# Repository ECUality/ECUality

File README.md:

# ECUality

This project is about taking full control of a dated fuel-injection system, and making that process easier to repeat. Currently, the system is built to run the engine in a 1984 VW vanagon. I aim to create a platform that bears adaptation requiring a minimum of external tools. 

ECUality differs from other ECU projects in that I avoid relying on complex tuning software, favoring simple map-tuning algorithms that run whenever the engine and O2 sensor are warm. 

More info [here](https://hackaday.io/project/4622-ecuality1).

## Install

1. Install the [Arduino IDE](https://www.arduino.cc/en/Main/Donate).
2. Clone the repository.
3. Connect an Arduino Mega 2560 to your computer's USB port.
4. Start the Arduino IDE.
5. Open `ECUality.ino` in the IDE.
6. Click "Upload". This will build the project, and upload the compiled firmware to your Arduino.

## License
[GNU GPLv3](LICENSE.txt)

## Dependencies
Platform: 8-bit Arduino Mega 2560 (The chip is AtMega 2560), atop the ECU shield specified in the shcematic and layout files.  
Build: Arduino IDE (uses gcc toolchain)

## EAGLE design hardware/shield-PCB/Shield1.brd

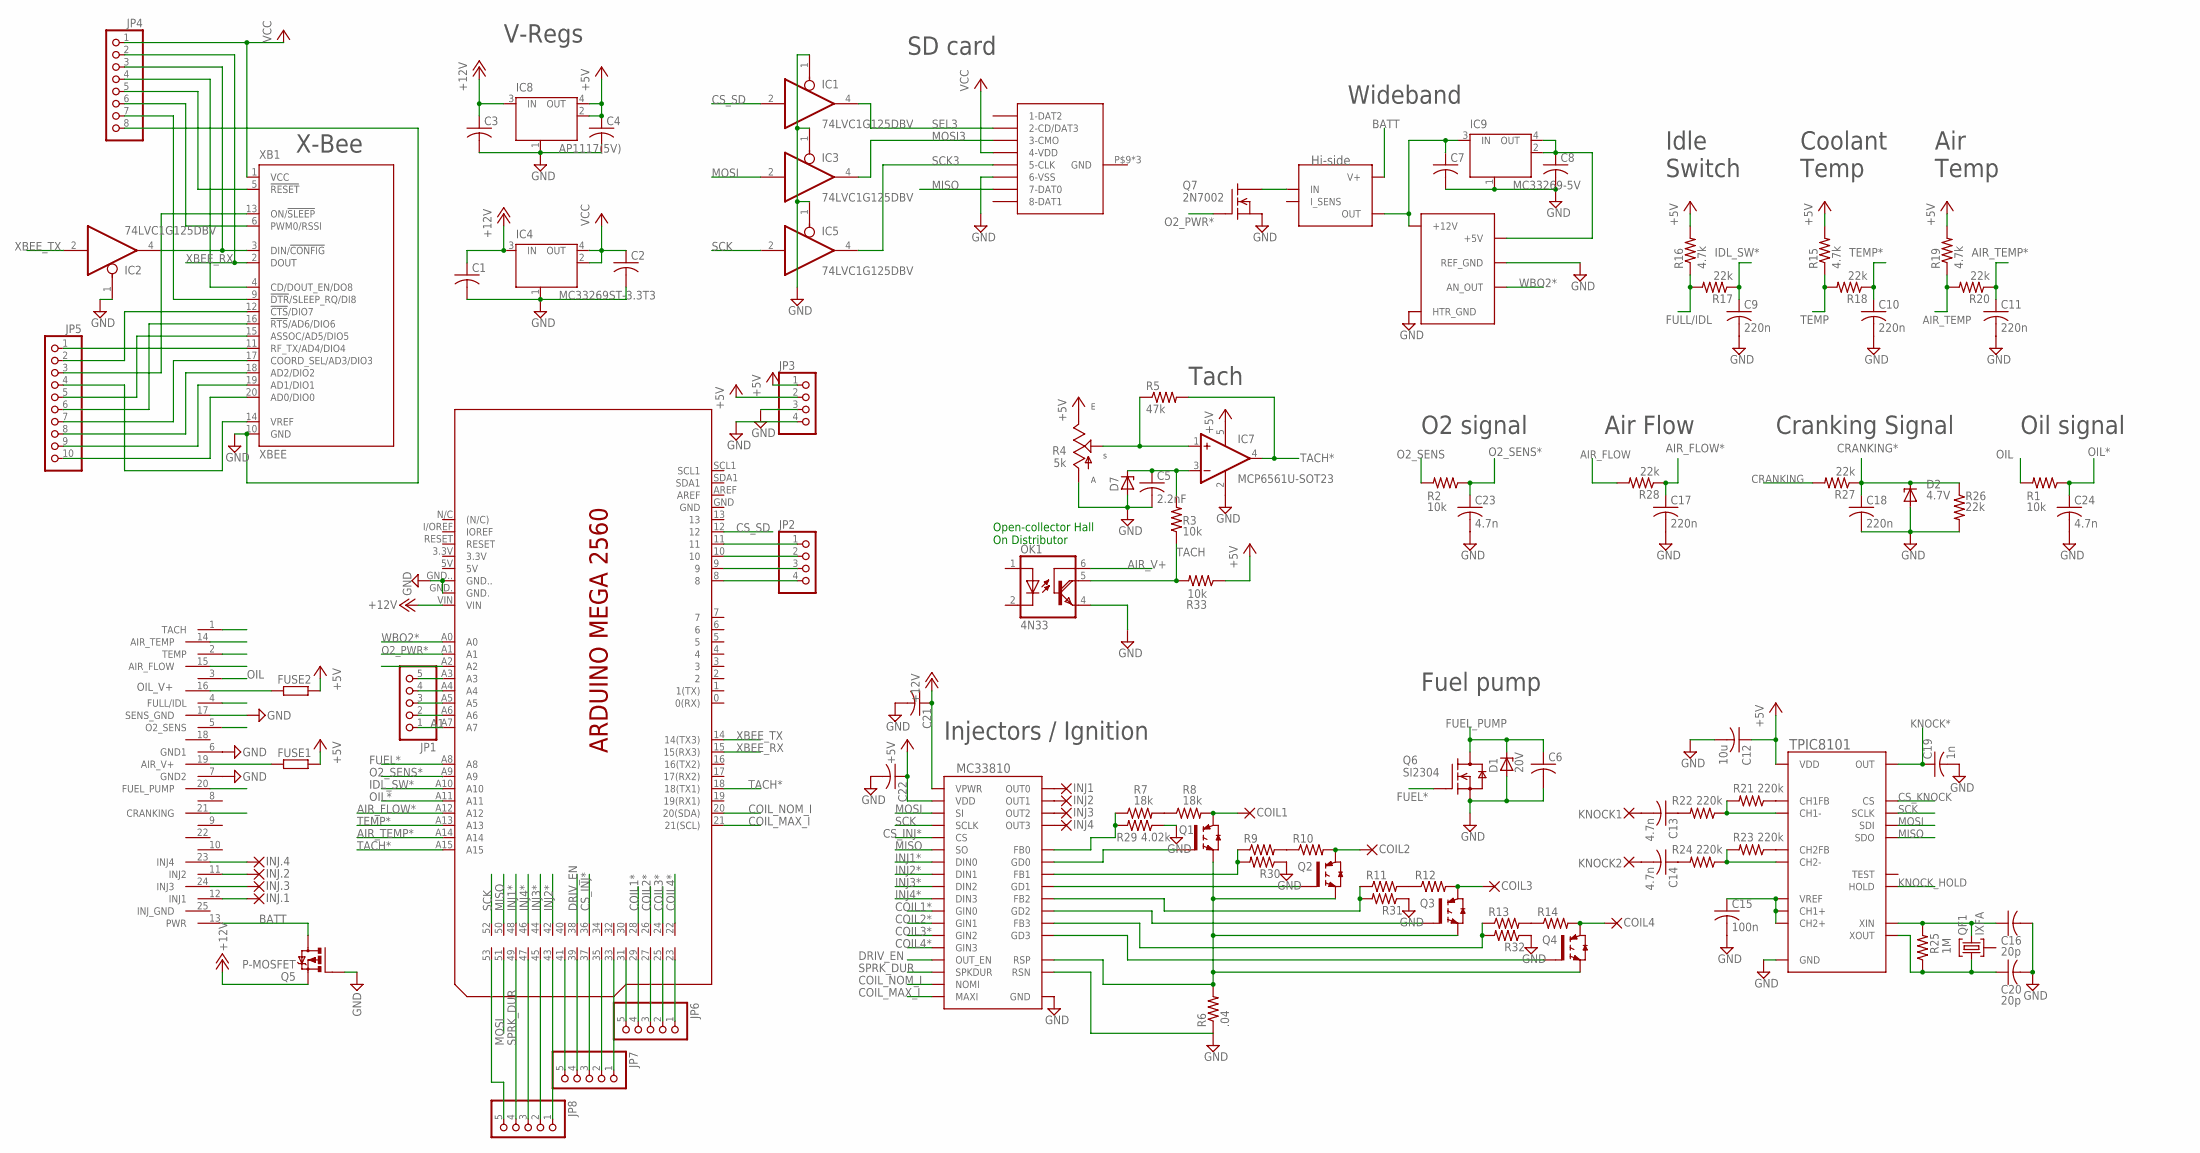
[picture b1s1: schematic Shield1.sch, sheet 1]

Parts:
C1, C2, C3, C4, C6, C7, C8, C21, C22: C-USC1206; C1206
C5: 2.2nF; C1206
C9, C10, C11, C17, C18: 220n; C1206
C12: 10u; C1206
C13, C14, C23, C24: 4.7n; C1206
C15: 100n; C1206
C16, C20: 20p; C1206
C19: 1n; C1206
COIL1, COIL2, COIL3, COIL4: 2,15/1,0
D1: 20V; SOD123
D2: 4.7V; SOD123
D7: ZENER-DIODESOD80C; SOD80C
FUSE1, FUSE2: R-EU_R1206W; R1206W
IC1, IC2, IC3, IC5: 74LVC1G125DBV; SOT23-5
IC4: MC33269ST-3.3T3; SOT223
IC6: MC33810SSOP; SSOP32_POWERPAD
IC7: MCP6561U-SOT23; SOT23-5
IC8: AP1117(5V); SOT223
IC9: MC33269-5V; SOT223
IC11: KNOCK_SENS_IC_TPIC8101; SO20L
INJ1, INJ2, INJ3, INJ4, INJ.1, INJ.2, INJ.3, INJ.4: 2,15/1,2
JP1, JP6, JP7, JP8: PINHD-1X5; 1X05
JP2, JP3: PINHD-1X4; 1X04
JP4: PINHD-1X8; 1X08
JP5: PINHD-1X10NARROW; 1X10-N
KNOCK1, KNOCK2: 2,15/1,0
OK1: 4N33; DIL06
Q1, Q2, Q3, Q4: ISL9V5036S3S; D2PACK
Q5: P-MOSFET; D-PAK_TO252AA
Q6: SI2304; SOT23
Q7: 2N7002; SOT23
Q8: BTS6133; DPACK_5
QF1: IXFA; HC49U
R1, R2, R3, R33: 10k; R1206
R4: 5k; 50/45J
R5: 47k; R1206
R6: .04; 0840/27
R7, R8: 18k; R1210W
R9, R10, R11, R12, R13, R14: R-US_R1210W; R1210W
R15, R16, R19: 4.7k; R1206
R17, R18, R20, R26, R27, R28: 22k; R1206
R21, R22, R23, R24: 220k; R1206
R25: 1M; R1206
R29: 4.02k; R1206
R30, R31, R32: R-US_R1206; R1206
U$1: VW_84_CONN
U$3: HI-ROSE-DM3D; DM3D-SF
U$4: ECOTRON_ALM-BOARD; ECOTRONS_ALM-BOARD
U$9: MEGA2560_SMD; MEGA_NO-PWR/USB/ICSP_SMD
XB1: XBEE

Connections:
+5V: C4.1, C12.1, C22.1, FUSE1.2, FUSE2.2, IC6.8 (VDD), IC7.5 (V+), IC8.2 (OUT), IC8.4 (OUT), IC11.1 (VDD), JP3.1, JP3.2, R4.1 (E), R15.2, R16.2, R19.2, R33.1
+12V: C1.1, C3.1, C21.1, IC4.3 (IN), IC6.25 (VPWR), IC8.3 (IN), Q5.3 (S), U$9.VIN
A1: JP1.1, U$9.A7
AIR_FLOW: R28.2, U$1.15 (AIR_FLOW)
AIR_FLOW*: C17.1, R28.1, U$9.A12
AIR_TEMP: R19.1, R20.2, U$1.14 (AIR_TEMP)
AIR_TEMP*: C11.1, R20.1, U$9.A14
AIR_V+: FUSE1.1, OK1.6 (B), U$1.19 (AIR_V+)
BATT: Q5.4 (D), Q8.3 (V+), U$1.13 (PWR)
COIL1: COIL1.1, Q1.2 (C), R8.2
COIL1*: IC6.24 (GIN0), U$9.28
COIL2: COIL2.1, Q2.2 (C), R10.2
COIL2*: IC6.23 (GIN1), U$9.26
COIL3: COIL3.1, Q3.2 (C), R12.2
COIL3*: IC6.22 (GIN2), U$9.24
COIL4: COIL4.1, Q4.2 (C), R14.2
COIL4*: IC6.21 (GIN3), U$9.22
COIL_MAX_I: IC6.29 (MAXI), U$9.21 (21(SCL))
COIL_NOM_I: IC6.28 (NOMI), U$9.20 (20(SDA))
CRANKING: R27.2, U$1.21 (CRANKING)
CRANKING*: C18.1, D2.C, R26.1, R27.1
CS_INJ*: IC6.4 (CS), U$9.36
CS_KNOCK: IC11.8 (CS)
CS_SD: IC1.2 (I), U$9.12
DRIV_EN: IC6.9 (OUT_EN), U$9.38
FUEL*: Q6.1 (G), U$9.A8
FUEL_PUMP: C6.1, D1.C, Q6.3 (D), U$1.20 (FUEL_PUMP)
FULL/IDL: R16.1, R17.2, U$1.4 (FULL/IDL)
GND: C1.2, C2.2, C3.2, C4.2, C5.2, C6.2, C7.2, C8.2, C9.2, C10.2, C11.2, C12.2, C15.2, C16.2, C17.2, C18.2, C19.2, C20.2, C21.2, C22.2, C23.2, C24.2, D1.A, D2.A, D7.A, IC1.1 (OE), IC1.3 (GND), IC2.1 (OE), IC2.3 (GND), IC3.1 (OE), IC3.3 (GND), IC4.1 (GND/ADJ), IC5.1 (OE), IC5.3 (GND), IC6.27 (RSN), IC6.GND, IC6.V1 (GND), IC6.V2 (GND), IC6.V3 (GND), IC6.V4 (GND), IC6.V5 (GND), IC7.2 (V-), IC8.1 (GND/ADJ), IC9.1 (GND/ADJ), IC11.2 (GND), JP3.3, JP3.4, JP4.8, OK1.4 (E), Q5.1 (G), Q6.2 (S), Q7.2 (S), R4.3 (A), R6.1, R26.2, R29.1, R30.1, R31.1, R32.1, U$1.6 (GND1), U$1.7 (GND2), U$1.17 (SENS_GND), U$3.P$3 (6-VSS), U$3.P$9 (GND), U$3.P$10 (GND), U$3.P$11 (GND), U$4.P$2 (HTR_GND), U$4.P$3 (REF_GND), U$4.P$6 (REF_GND), U$4.P$9 (HTR_GND), U$9.GND., U$9.GND.., XB1.10 (GND)
IDL_SW*: C9.1, R17.1, U$9.A10
INJ1: INJ.1.1, U$1.12 (INJ1)
INJ1*: IC6.10 (DIN0), U$9.48
INJ2: INJ.2.1, U$1.11 (INJ2)
INJ2*: IC6.11 (DIN1), U$9.42
INJ3: INJ.3.1, U$1.24 (INJ3)
INJ3*: IC6.12 (DIN2), U$9.44
INJ4: INJ.4.1, U$1.23 (INJ4)
INJ4*: IC6.13 (DIN3), U$9.46
KNOCK*: C19.1, IC11.4 (OUT), U$9.A2
KNOCK_HOLD: IC11.7 (HOLD)
MISO: IC6.7 (SO), IC11.11 (SDO), U$3.P$2 (7-DAT0), U$9.50
MOSI: IC3.2 (I), IC6.6 (SI), IC11.12 (SDI), U$9.51
MOSI3: IC3.4 (O), U$3.P$6 (3-CMO)
unnamed: C5.1, D7.C, IC7.3 (-IN), R3.2
unnamed: C7.1, IC9.3 (IN), Q8.1 (OUT), Q8.5 (OUT), U$4.P$1 (+12V), U$4.P$10 (+12V)
unnamed: IC6.26 (RSP), Q1.3 (E), Q2.3 (E), Q3.3 (E), Q4.3 (E), R6.2
unnamed: IC6.14 (GD1), Q2.1 (G)
unnamed: IC6.2 (FB0), R7.1, R29.2
unnamed: IC6.3 (GD0), Q1.1 (G)
unnamed: Q7.3 (D), Q8.2 (IN)
unnamed: IC6.1 (OUT0), INJ1.1
unnamed: IC11.19 (CH1-), R21.2, R22.1
unnamed: IC7.1 (+IN), R4.2 (S), R5.1
unnamed: IC6.15 (FB1), R9.1, R30.2
unnamed: IC6.30 (GD2), Q3.1 (G)
unnamed: IC2.4 (O), JP4.3, XB1.3 (DIN/!CONFIG)
unnamed: C8.1, IC9.2 (OUT), IC9.4 (OUT), U$4.P$4 (+5V)
unnamed: IC6.31 (FB2), R11.1, R31.2
unnamed: IC6.19 (GD3), Q4.1 (G)
unnamed: IC11.18 (CH1FB), R21.1
unnamed: IC6.18 (FB3), R13.1, R32.2
unnamed: C13.1, R22.2
unnamed: IC11.16 (CH2-), R23.2, R24.1
unnamed: C14.1, R24.2
unnamed: C15.1, IC11.3 (VREF), IC11.15 (CH2+), IC11.20 (CH1+)
unnamed: IC11.17 (CH2FB), R23.1
unnamed: IC6.16 (OUT1), INJ2.1
unnamed: IC6.32 (OUT2), INJ3.1
unnamed: C20.1, IC11.10 (XOUT), QF1.1, R25.1
unnamed: C16.1, IC11.9 (XIN), QF1.3, R25.2
unnamed: IC6.17 (OUT3), INJ4.1
unnamed: C13.2, KNOCK1.1
unnamed: C14.2, KNOCK2.1
unnamed: JP6.1, U$9.23
unnamed: R7.2, R8.1
unnamed: R9.2, R10.1
unnamed: R11.2, R12.1
unnamed: R13.2, R14.1
unnamed: JP1.2, U$9.A6
unnamed: JP1.3, U$9.A5
unnamed: JP1.4, U$9.A4
unnamed: JP1.5, U$9.A3
unnamed: JP2.1, U$9.11
unnamed: JP2.2, U$9.10
unnamed: JP2.3, U$9.9
unnamed: JP2.4, U$9.8
unnamed: JP4.4, XB1.4 (CD/DOUT_EN/DO8)
unnamed: JP4.5, XB1.5 (!RESET)
unnamed: JP4.6, XB1.6 (PWM0/RSSI)
unnamed: JP5.10, XB1.20 (AD0/DIO0)
unnamed: JP5.9, XB1.19 (AD1/DIO1)
unnamed: JP5.8, XB1.18 (AD2/DIO2)
unnamed: JP5.7, XB1.17 (COORD_SEL/AD3/DIO3)
unnamed: JP5.6, XB1.16 (!RTS!/AD6/DIO6)
unnamed: JP5.5, XB1.15 (ASSOC/AD5/DIO5)
unnamed: JP5.4, XB1.14 (VREF)
unnamed: JP5.3, XB1.13 (ON/!SLEEP)
unnamed: JP5.2, XB1.12 (!CTS!/DIO7)
unnamed: JP5.1, XB1.11 (RF_TX/AD4/DIO4)
unnamed: JP4.7, XB1.9 (!DTR!/SLEEP_RQ/DI8)
unnamed: JP6.2, U$9.25
unnamed: JP6.3, U$9.27
unnamed: JP6.4, U$9.29
unnamed: JP6.5, U$9.31
unnamed: JP7.1, U$9.33
unnamed: JP7.2, U$9.35
unnamed: JP7.3, U$9.37
unnamed: JP7.4, U$9.39
unnamed: JP7.5, U$9.41
unnamed: JP8.1, U$9.43
unnamed: JP8.2, U$9.45
unnamed: JP8.3, U$9.47
unnamed: JP8.5, U$9.53
O2_PWR*: Q7.1 (G), U$9.A1
O2_SENS: R2.2, U$1.5 (O2_SENS)
O2_SENS*: C23.1, R2.1, U$9.A9
OIL: R1.2, U$1.3
OIL*: C24.1, R1.1, U$9.A11
OIL_V+: FUSE2.1, U$1.16
SCK: IC5.2 (I), IC6.5 (SCLK), IC11.13 (SCLK), U$9.52
SCK3: IC5.4 (O), U$3.P$4 (5-CLK)
SEL3: IC1.4 (O), U$3.P$7 (2-CD/DAT3)
SPRK_DUR: IC6.20 (SPKDUR), JP8.4, U$9.49
TACH: OK1.5 (COL), R3.1, R33.2, U$1.1 (TACH)
TACH*: IC7.4 (OUT), R5.2, U$9.18 (18(TX1)), U$9.A15
TEMP: R15.1, R18.2, U$1.2 (TEMP)
TEMP*: C10.1, R18.1, U$9.A13
VCC: C2.1, IC1.5 (VCC), IC2.5 (VCC), IC3.5 (VCC), IC4.2 (OUT), IC4.4 (OUT), IC5.5 (VCC), JP4.1, U$3.P$5 (4-VDD), XB1.1 (VCC)
WBO2*: U$4.P$7 (AN_OUT), U$9.A0
XBEE_RX: JP4.2, U$9.15 (15(RX3)), XB1.2 (DOUT)
XBEE_TX: IC2.2 (I), U$9.14 (14(TX3))

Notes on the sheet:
Tach
Fuel pump
SD card
O2 signal
Injectors / Ignition
X-Bee
V-Regs
Wideband
Idle Switch
Air Temp
Coolant Temp
Air Flow
Cranking Signal
Oil signal
Open-collector Hall On Distributor

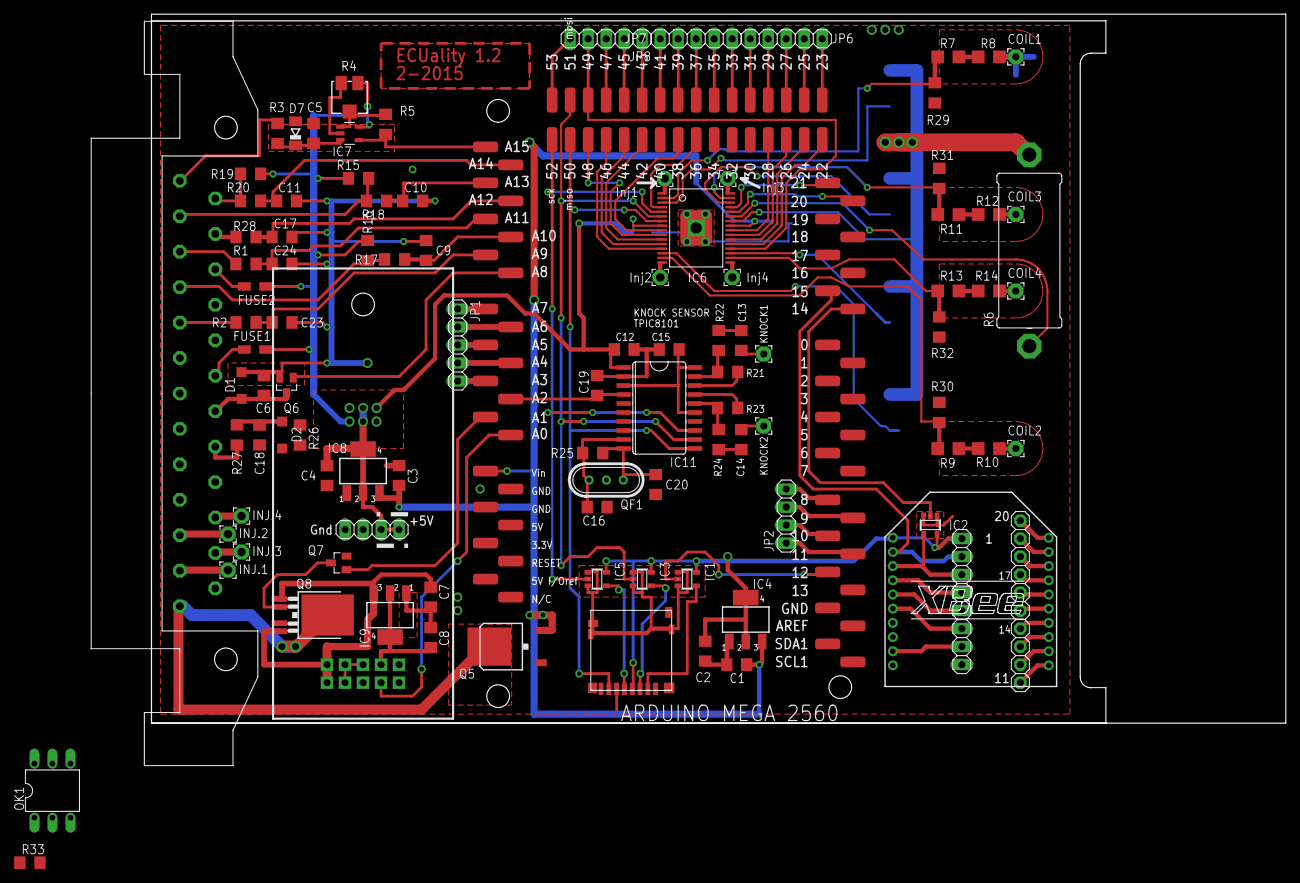
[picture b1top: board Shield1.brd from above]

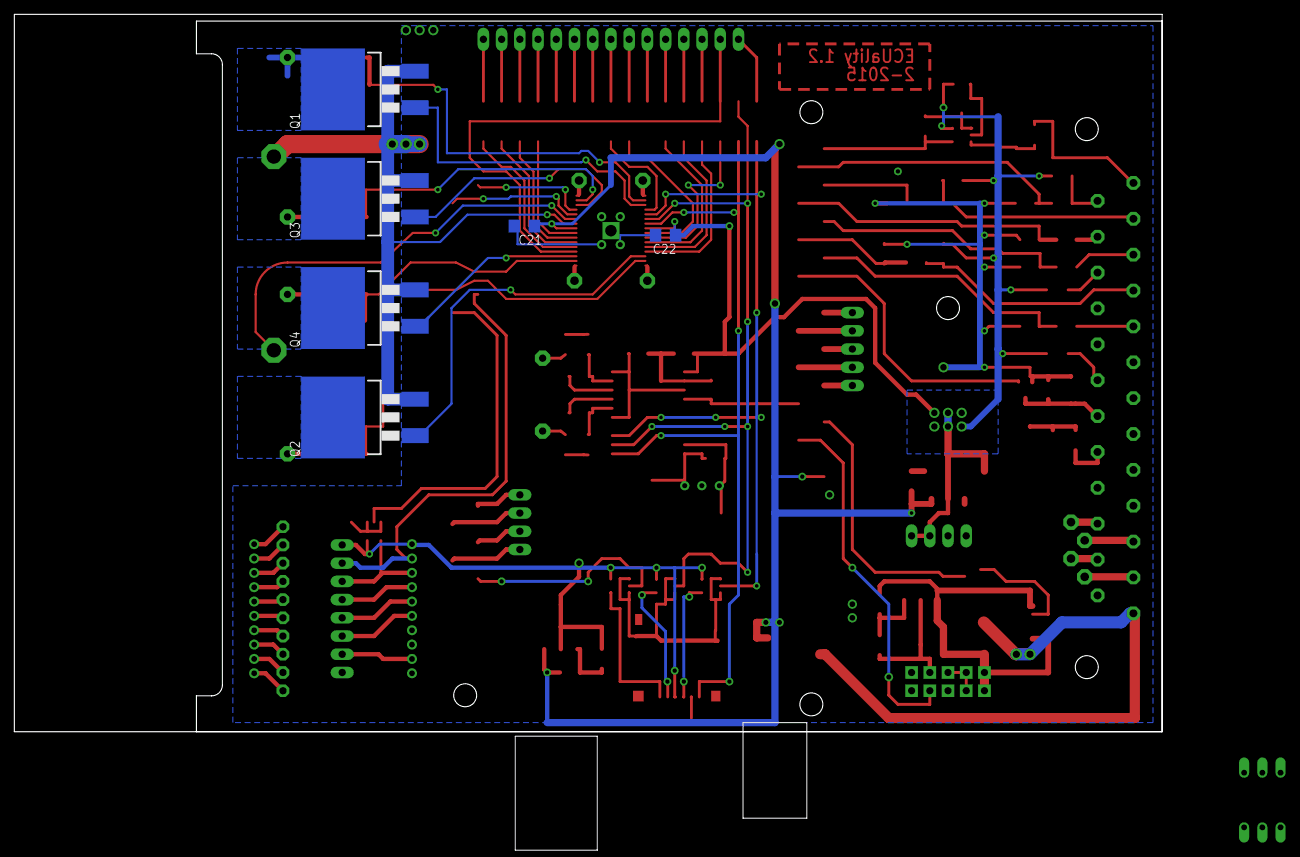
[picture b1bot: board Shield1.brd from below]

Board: 2 copper layers, 160.0 x 100.0 mm, 109 parts (7 on the bottom side), 129 nets.

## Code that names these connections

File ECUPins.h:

#pragma once

// Pin mappings /////////////////

// Input pins
const uint8_t air_flow_pin = A12;
const uint8_t air_temp_pin = A14;
const uint8_t o2_pin = A9;
const uint8_t coolant_temp_pin = A13;
const uint8_t oil_pressure_pin = A11;
const uint8_t tach_pin = 18;
const uint8_t tach_interrupt = 5;		// see "attachinterrupt" page on Arduino.cc
const uint8_t coil_current_interrupt = 3;	// same as above www.arduino.cc
const uint8_t idl_full_pin = A10;
const uint8_t cranking_pin = 10;
const uint8_t coil_nom_i = 20;
const uint8_t coil_max_i = 21;

const uint8_t inputs[] = { air_flow_pin, air_temp_pin, o2_pin, coolant_temp_pin, oil_pressure_pin, tach_pin,
idl_full_pin, cranking_pin, coil_nom_i, coil_max_i, '\0' };

// Output pins
const uint8_t inj2_pin = 42;
const uint8_t inj3_pin = 44;
const uint8_t inj4_pin = 46;
const uint8_t inj1_pin = 48;

const uint8_t coil1_pin = 28;
const uint8_t coil2_pin = 26;
const uint8_t coil3_pin = 24;
const uint8_t coil4_pin = 22;

const uint8_t fuel_pin = A8;
const uint8_t drv_en_pin = 38;
const uint8_t o2_pwr_pin = A1;
const uint8_t cs_knock_pin = 9;
const uint8_t cs_sd_pin = 12;
const uint8_t cs_inj_pin = 36;
const uint8_t inj_led_pin = 25;

uint8_t outputs[] = { inj1_pin, inj2_pin, inj3_pin, inj4_pin,
coil1_pin, coil2_pin, coil3_pin, coil4_pin,
fuel_pin, drv_en_pin, o2_pwr_pin,
cs_knock_pin, cs_sd_pin, cs_inj_pin, inj_led_pin, '\0' };

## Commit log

2015-02-24 :neckbeard: Added .gitattributes & .gitignore files
2015-03-16 Updated .gitignore for Visual Studio
    Removed some ignore lines for packages I don't need.
2015-03-16 Adding TimerOne-r11 library
2015-03-16 Adding first engine map
    This is from ECU\test\VW_characterize
2015-03-16 Nested interrupts working
2015-03-16 Update .gitignore for Visual Micro
2015-03-16 Wrapping in VS solution
2015-03-17 Scheduler working
2015-03-17 Switched to Atmel Studio
    Visual Studio Community 2013 started crashing repeatedly, starting with
    the first compile-upload to the mega 2560
2015-03-17 loading Map to memory
2015-03-19 Switch back to VS13 community
    For memory and load speed reasons. This is verified to blink correctly
    using scheduler
2015-03-20 Serial Map input working
    Also, formatting described and formatted text file containing map
    updated.
2015-03-23 map EEPROM load/save working
2015-03-23 Pulse ISR's added, code cleaned
    removed non-used EE functions and hard-coded map function
2015-03-28 Pulse working, Interpolate written
    Pulse still has 7us interrupt conflict with other Arduino interrupts.
    Interpolate not tested.
2015-03-29 Map timings reproduced, TimerOne removed
    handled off-map cases and renamed some things
2015-03-30 Building post decomp attempt
    Learned: arduino has problems with "extern" and I should really try this
    with a simple program first.
2015-03-31 Manual controls and storage parameters
    building and working
2015-04-01 Pins mapped, outputs working
    injector driver is behaving, injector LED added. Also fixed bug where
    "coasting" just left the injectors open, and inverted full_idle input.
2015-04-02 Array-Scaling for Sensors and Choke
    Also added new choke scale to serial and eeprom for updating saving
    reporting and loading
2015-04-02 Starting and running.
    Boo-yah. Corrected drv_en_pin. Added auto. inj_dur readout during
    cranking. Tuned cranking_dur to 1350
2015-04-06 Map, ECUSerial classes building
    but not tested
2015-04-06 Added EEIndex, Scale classes
    Not tested yet, but building and communicating. Known issue with
    EEIndex having two initial zeros.
2015-04-09 Added Parameter class
    building and communicating predictably, but I'm still re-factoring so
    this is not deployed.
2015-04-09 Added ECUSerial command-list
    Building and working on tester, but still big and a little ugly.
    Commands can't be batched.
2015-04-11 Improved serial command parsing
    Now rejects leading spaces, allowing commands to be strung together,
    making it more convenient to load a bunch of parameters and maps.
2015-04-14 Added Tweaker, drove block
    Still has issue with local offsets drifting.
2015-04-14 Fixed signs in fuel tweaking mode 3
    Local and global tweaks road-tested drivable. Still need to fix stopped
    rpm detection.
2015-04-21 Improve idle tuning (using RPM only now)
    Currently using the move-lean until rpm drops, then step back approach.
    This is used whether engine is warm or not. Very drive-able.
2015-05-07 Added support for wireless
    still has a bug with auto-reporting
2015-05-19 Wireless reporting oil
2015-06-24 Some idle separation code, fault detection
    I separated idle into a single number, then pulled that out again
    because it wasn't stable
2015-06-26 IR remote added, reporting formatted to LCD
    Also moved variables to Globals.h and protocol to Protocol.h
2015-07-15 Interoperability of Serial and Serial3
    Now, when a command is received on either serial port, the reply is on
    that serial port, but then future automatic responses go back to being
    on the default port. HSerial is now a pointer, not a reference.
2016-03-05 Comments describing execution priority
    Also a known get-there version
2016-03-07 Paramater master lists
    To vastly simplify the adding, removing, renaming of Parameter and Scale
    objects
2016-03-15 Changed coasting/idling and not running conditions
    Also adjusted the map and added out-of-bounds check for new scales
2016-03-15 Store Param/Scale names as F("text")
    This saves on memory as I add parameters
2016-03-15 Updating data
    removing unused Parameters/Scales also
2016-03-16 IR remote can now adjust all Params/Scales
    Also added theft prevention
2016-11-06 Cold engine idle bugfix
    Adds cold-engine enrichment while idling.
2016-11-07 Talking over SPI to MC33810
    Setting dwell timeout for ignition and added command to check status of
    both ignition and injection sides
2016-11-08 Driving ignition coil
    And measuring coil current, and handling start-up conditions.
2016-11-08 Fixed ignition phase
    Now triggering on the falling edge of the tach signal (the schmitt
    inverts it)
2016-11-10 More agressive sparks for starting
2016-11-19 Starting spark trouble WIP
2016-11-21 Change Tach input... Engine now starts
    The tach input was previously sourced from the the old ignition driver,
    which missed every 3rd or every other trigger event while the starter
    was cranking. This prevented the ECU from producing accurate dwell
    times while cranking. We now source timing directly from the hall
    effect (a wiring change in the harness), which produces the expected,
    consistent square wave. The signal is inverted, so we're back to rising
2017-04-04 Speed up Dwell/RPM timer
    Switching to a new coil with lower primary resistance, I was charging
    this coil to high currents much faster. So the Dwell setting needed to
    be more accurate, so I dropped the prescale from 1/1024 to 1/256.
2017-04-05 New E-core coil / Tweak lockout persistent
    I-max for coil set to 16A / SetNomI() command added to help measure coil
    current on bench / Tweak-lock "lock" moved out of Tweaker class / Tweak
    lockout made persistent (EEPROM) / Dwell parameter limits changed /
    Parameter file updated.
2018-07-12 WIP: auto-tune upgrade/debug
    global correction now scales with nominal injector duration, every
    adjustment (tweak) affects both the global correction and local map (no
    more switching between local/global based on local_sum_limit logic).
    Distribution of correction to local map is now coarser but more
    deterministic (no integer division errors).
2018-07-12 Fixed type mismatch of rpm var in tweaker class
    The rpm variable is passed by reference to the boss object (FuelTweaker
    class). The FuelTweaker class was expecting a reference to a signed
    int, but it was given a reference to an unsigned int. So boss was
    always seeing an erroneous rpm value, which totally buggered where the
    changes to the local map were going.
2018-07-12 Tidy up:
    Got rid of local_sum_limit parameter. Renamed step_size parameter to
    local_step_size. Adjusted EE data to reflect new acceptable ranges and
    good defaults and removal of local_sum_limit.
2018-07-12 Touching up parameter loading
    the "2" in the O2 parameter descriptions threw off the loading of data -
    TimedParseInt() saw the 2 as an int. So I replaced "O2" with "Oxy" and
    also nudged a few numbers.
2018-07-30 Add .travis.yml for automated builds :)
2018-07-30 fix travis build
2018-07-30 Who knows?
2018-07-30 Add readme
2018-07-30 create engine_data directory
2018-07-30 Fix engine_data readme table
2018-07-30 remove deleted files, add license
2018-07-30 Adding skeleton to README
2018-07-30 Move core code in to core directory.
2018-07-30 Adhere to Arduino dumb naming convention.
2018-07-30 don't build the dash-monitor in travis
2019-02-07 Adding Ign. timing Initial try
    Timing calculation working. Interrupts not working.
2019-02-07 Fixed overflow on multiplication bug
    timing is now looking good on scope.
2019-02-07 Closing another data race
2019-09-09 bugfix: overflow reg. update when cranking
    Injector duration calculation function was prematurely returning when the "Cranking" condition (as in, the starter motor is turning the engine) was true.
2019-09-10 Add simulated tach, on/off control of coil/inject
    These are tools to assist tracking down an electrical noise issue. With simulated Tach signal, I can run the various outputs of the ECU without the engine actually running. With on-off control of the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
2019-09-10 Add prototype of new addTask() minor refactor
2019-09-11 Fixing bug with scheduled tasks
    Simulated Tach and control over coil, injectors and fuel pump now work
2019-09-12 Add report when Serial port changes
2019-11-14 Coil on plug coded but not starting
    Tested working with the lathe spinning the distributor, but on van,
    does not work. Appears the timing is not consistent. Van will catch
    a stroke or two, and subsequently stop, and with continued cranking,
    occasionally kick back as though spark is too advanced.
2019-11-15 Replace digitalRead() for cyl index check
    Now using PINA for direct port manipulation. Added various comments.
2019-11-18 Indexed Cylinder timing fixed
    Previously, the cylinder Cylinder 1 selection was handled in Tach-edge
    interrupt, and cylinder switching 1-to-2-to-3-to-4 was handled on
    dwell interrupt (TMR4/5). Sometimes the dwell interrupt happened
    just before the tach-edge, sometimes just after. This would mess up
    timing. To solve, I moved all cylinder select logic to tach-edge isr.
2019-12-08 Moving advance curves to scales
    rad and vad are the handles
2019-12-31 added initial_retard parameter
    Also renamed some variables for readability and adjusted how
    spark_position gets calculated to make use of the new parameter.
2019-12-31 Dwell now auto-adjusted to NOMI
    Auto-7 output now prints dwell. NOMI pin is measured on spark,
    if it's high, then g_dwell gets decremented. If it's low,
    g_dwell gets incremented. nom_coil_current is now a parameter.
    with range 0-31 where 0 = 3.0A and each tic is .25A more.
2020-01-20 Started CodeDoc.doc
2021-01-03 Clean up Readme
2021-01-03 Add shield design and reference
2021-05-29 Update schematic to show tach power and pullup
